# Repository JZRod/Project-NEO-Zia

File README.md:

# Project NEO Zia
This circut board is intended to make the New Mexico Zia out of LED's 
There is a [PDF](assets/README.pdf) version of this doccument in the assets folder

## Using the board
This section goes over information on how to configure, wire, and mount the board. 
### Configuration
This PCB is designed to accept power from an external 12 volt input. It is also able to recieve power from a 5 volt PWM cable. By default the board is configured to recieve power from the 12 volt external power input.  
- For the PWM power input open JP1 and bridge JP2
- For external power input open JP2 and bridge JP1  

> **NEVER BRIDGE BOTH JUMPERS AT ONCE**
### Wiring
#### External Power Input
The external power input can accept voltages between 5 and 12 volts. When using the external power input fuse it at a maximum of 5 amps.  

#### PWM Connections
There are two PWM connections on the board. One is a PWM output and one is an input. The output connector outputs a PWM signal after it has passed through all LED's. If you want to power the board with the PWM connection refer to the configuration section of this doccument.  

>- The PWM output connector outputs whatever voltage it is provided through the PWM input  
>- The PWM output **does not touch the voltage regulator on the board at all**  
>- The pinout of these connectors is also labeled on the board  
### Programming
This board uses a standard NeoPixel PWM signal. The PWM output connector is connected to the DATA OUT pin on the last NeoPixel in the chain. The PWM input connector is connected to the DATA IN pin on the first NeoPixel in the chain. 
> The DATA IN/OUT pins do not have any protection on them  
>   The pinout for the PWM In/Out connecters can be seen in the Wiring section of this document
More information about these NeoPixels can be found in their [datasheet](https://cdn-shop.adafruit.com/product-files/1655/SKC6812RV__12VOP0274E_REV.A1_EN%2812%29.pdf)
#### NeoPixel Layout
The drawing below shous the pattern in which the NeoPixels are wired  
The PWM Input is connected to D68 and goes to each NeoPixel in a decreasing order. When the signal reaches D1 it is connected to the PWM Output connector.  

The black line starts at D68 and goes around the board in the same way the PWM signal is routed until it reaches D1.
> The DATA Out pin of D1 is wired to Pin 3 of the PWM Output Connector
### Mounting
On the newest revisions the 4 center holes are 3/16 and sized for 10/24 screws. Each revision has a STEP file in it's folder.  
> For all revisions, I would suggest that you check the mounting hole spacing and size in the CAD model
## Manufacturing
If you want to make this board you can either use the pre-made gerber files or customize them using the KiCad project files. All these files are available in the revision folders. The latest version can also be found on the releases page.
### Pre-Made Gerbers
In each revision folder there are zip files. These are the Gerber's, and you should be able to drop them straight in you PCB manufacturing service.  
> Some PCB manufacturing services will accept the bare KiCad PCB file.   
>**Read the REVISION NOTES.txt for info on what changed between each revision** 
### Customization  
If you want to customize this board each revision folder has a KiCad project file, a KiCad PCB File, and a KiCad Schematic file. 
> I suggest you use KiCad 9 or higher.  
>**Read the [REVISION NOTES.txt](Revisions/REVISION$20NOTES.txt) for info on what changed between each revision**  
## Credit  
**Designed by Josh Rodriguez for FIRST Robotics Competition Team 1164 Project NEO**

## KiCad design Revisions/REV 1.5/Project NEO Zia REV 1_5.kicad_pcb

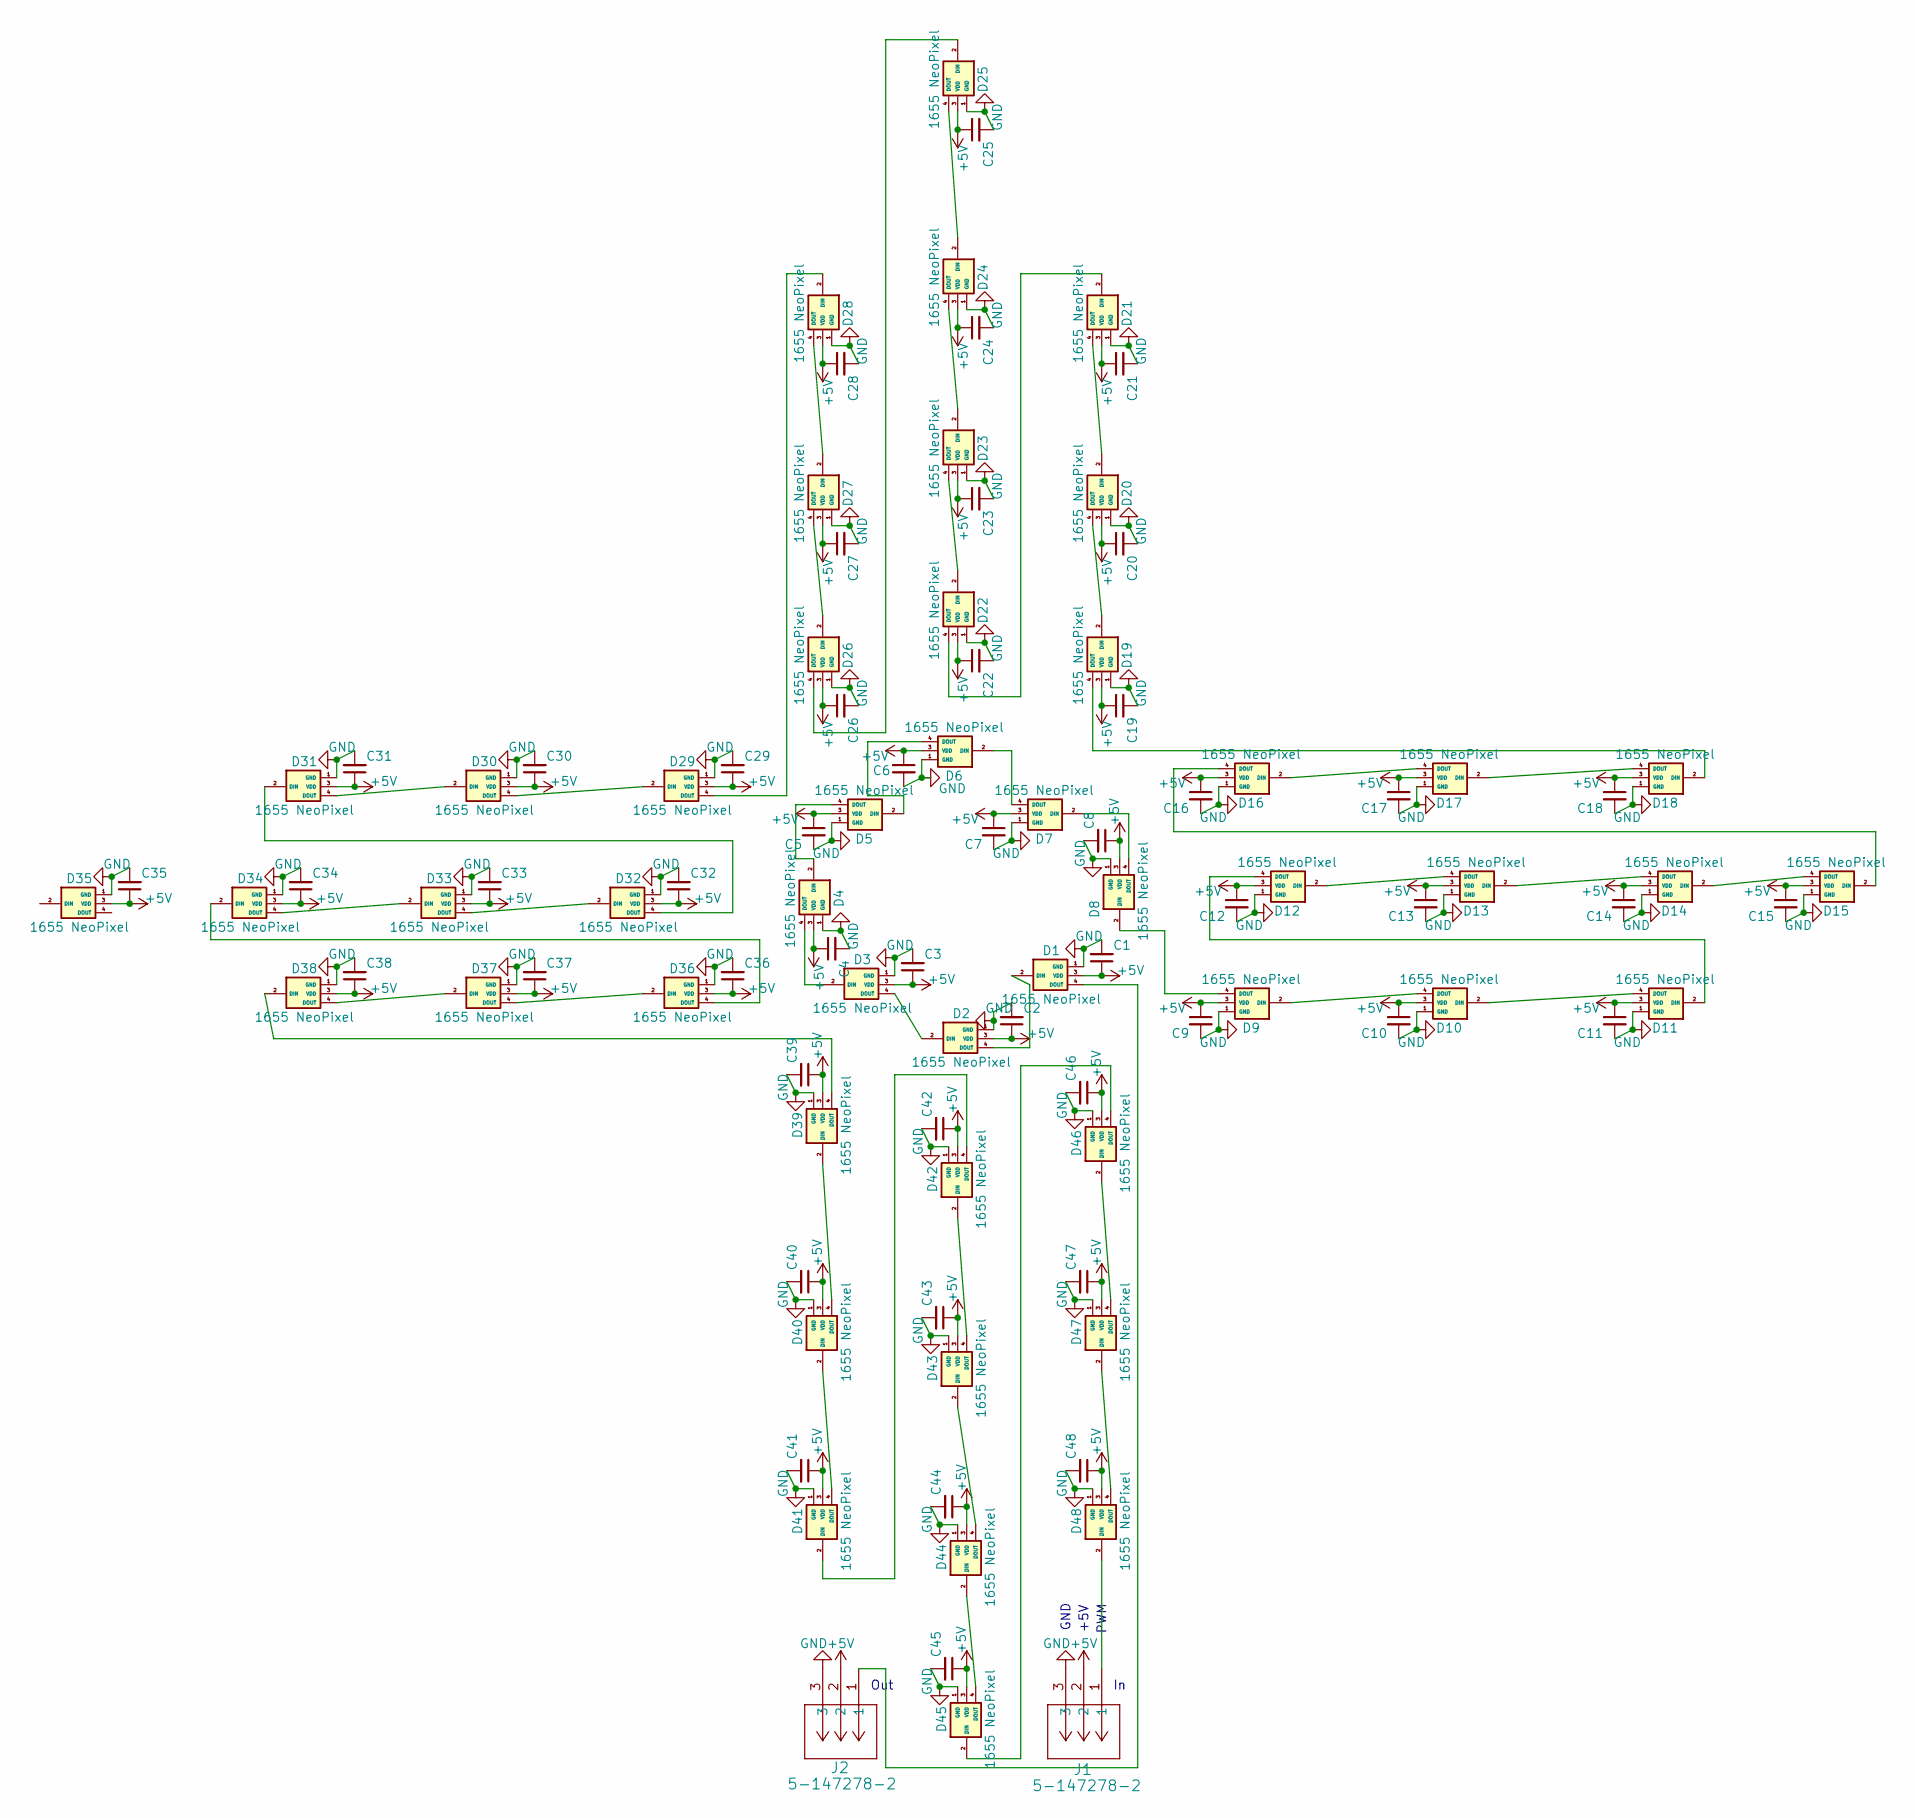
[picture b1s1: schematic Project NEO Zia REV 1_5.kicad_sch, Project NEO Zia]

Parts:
C1, C2, C3, C4, C5, C6, C7, C8, C9, C10, C11, C12, C13, C14, C15, C16, C17, C18, C19, C20, C21, C22, C23, C24, C25, C26, C27, C28, C29, C30, C31, C32, C33, C34, C35, C36, C37, C38, C39, C40, C41, C42, C43, C44, C45, C46, C47, C48: C_Small; CAPC1005X55N
D1, D2, D3, D4, D5, D6, D7, D8, D9, D10, D11, D12, D13, D14, D15, D16, D17, D18, D19, D20, D21, D22, D23, D24, D25, D26, D27, D28, D29, D30, D31, D32, D33, D34, D35, D36, D37, D38, D39, D40, D41, D42, D43, D44, D45, D46, D47, D48: 1655 NeoPixel; LED_1655; PARTREV 01
J1, J2: 5-147278-2; CONN3_5-147278-2_TEC

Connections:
+5V: C1.1, C2.1, C3.1, C4.1, C5.1, C6.1, C7.1, C8.1, C9.1, C10.1, C11.1, C12.1, C13.1, C14.1, C15.1, C16.1, C17.1, C18.1, C19.1, C20.1, C21.1, C22.1, C23.1, C24.1, C25.1, C26.1, C27.1, C28.1, C29.1, C30.1, C31.1, C32.1, C33.1, C34.1, C35.1, C36.1, C37.1, C38.1, C39.1, C40.1, C41.1, C42.1, C43.1, C44.1, C45.1, C46.1, C47.1, C48.1, D1.3 (VDD), D2.3 (VDD), D3.3 (VDD), D4.3 (VDD), D5.3 (VDD), D6.3 (VDD), D7.3 (VDD), D8.3 (VDD), D9.3 (VDD), D10.3 (VDD), D11.3 (VDD), D12.3 (VDD), D13.3 (VDD), D14.3 (VDD), D15.3 (VDD), D16.3 (VDD), D17.3 (VDD), D18.3 (VDD), D19.3 (VDD), D20.3 (VDD), D21.3 (VDD), D22.3 (VDD), D23.3 (VDD), D24.3 (VDD), D25.3 (VDD), D26.3 (VDD), D27.3 (VDD), D28.3 (VDD), D29.3 (VDD), D30.3 (VDD), D31.3 (VDD), D32.3 (VDD), D33.3 (VDD), D34.3 (VDD), D35.3 (VDD), D36.3 (VDD), D37.3 (VDD), D38.3 (VDD), D39.3 (VDD), D40.3 (VDD), D41.3 (VDD), D42.3 (VDD), D43.3 (VDD), D44.3 (VDD), D45.3 (VDD), D46.3 (VDD), D47.3 (VDD), D48.3 (VDD), J1.2, J2.2
GND: C1.2, C2.2, C3.2, C4.2, C5.2, C6.2, C7.2, C8.2, C9.2, C10.2, C11.2, C12.2, C13.2, C14.2, C15.2, C16.2, C17.2, C18.2, C19.2, C20.2, C21.2, C22.2, C23.2, C24.2, C25.2, C26.2, C27.2, C28.2, C29.2, C30.2, C31.2, C32.2, C33.2, C34.2, C35.2, C36.2, C37.2, C38.2, C39.2, C40.2, C41.2, C42.2, C43.2, C44.2, C45.2, C46.2, C47.2, C48.2, D1.1 (GND), D2.1 (GND), D3.1 (GND), D4.1 (GND), D5.1 (GND), D6.1 (GND), D7.1 (GND), D8.1 (GND), D9.1 (GND), D10.1 (GND), D11.1 (GND), D12.1 (GND), D13.1 (GND), D14.1 (GND), D15.1 (GND), D16.1 (GND), D17.1 (GND), D18.1 (GND), D19.1 (GND), D20.1 (GND), D21.1 (GND), D22.1 (GND), D23.1 (GND), D24.1 (GND), D25.1 (GND), D26.1 (GND), D27.1 (GND), D28.1 (GND), D29.1 (GND), D30.1 (GND), D31.1 (GND), D32.1 (GND), D33.1 (GND), D34.1 (GND), D35.1 (GND), D36.1 (GND), D37.1 (GND), D38.1 (GND), D39.1 (GND), D40.1 (GND), D41.1 (GND), D42.1 (GND), D43.1 (GND), D44.1 (GND), D45.1 (GND), D46.1 (GND), D47.1 (GND), D48.1 (GND), J1.3, J2.3
unnamed: D1.2 (DIN), D2.4 (DOUT)
unnamed: D1.4 (DOUT), J2.1
unnamed: D2.2 (DIN), D3.4 (DOUT)
unnamed: D3.2 (DIN), D4.4 (DOUT)
unnamed: D4.2 (DIN), D5.4 (DOUT)
unnamed: D5.2 (DIN), D6.4 (DOUT)
unnamed: D6.2 (DIN), D7.4 (DOUT)
unnamed: D7.2 (DIN), D8.4 (DOUT)
unnamed: D8.2 (DIN), D9.4 (DOUT)
unnamed: D10.2 (DIN), D11.4 (DOUT)
unnamed: D9.2 (DIN), D10.4 (DOUT)
unnamed: D11.2 (DIN), D12.4 (DOUT)
unnamed: D12.2 (DIN), D13.4 (DOUT)
unnamed: D13.2 (DIN), D14.4 (DOUT)
unnamed: D14.2 (DIN), D15.4 (DOUT)
unnamed: D15.2 (DIN), D16.4 (DOUT)
unnamed: D16.2 (DIN), D17.4 (DOUT)
unnamed: D17.2 (DIN), D18.4 (DOUT)
unnamed: D18.2 (DIN), D19.4 (DOUT)
unnamed: D19.2 (DIN), D20.4 (DOUT)
unnamed: D20.2 (DIN), D21.4 (DOUT)
unnamed: D21.2 (DIN), D22.4 (DOUT)
unnamed: D22.2 (DIN), D23.4 (DOUT)
unnamed: D23.2 (DIN), D24.4 (DOUT)
unnamed: D24.2 (DIN), D25.4 (DOUT)
unnamed: D25.2 (DIN), D26.4 (DOUT)
unnamed: D26.2 (DIN), D27.4 (DOUT)
unnamed: D27.2 (DIN), D28.4 (DOUT)
unnamed: D28.2 (DIN), D29.4 (DOUT)
unnamed: D29.2 (DIN), D30.4 (DOUT)
unnamed: D30.2 (DIN), D31.4 (DOUT)
unnamed: D31.2 (DIN), D32.4 (DOUT)
unnamed: D32.2 (DIN), D33.4 (DOUT)
unnamed: D33.2 (DIN), D34.4 (DOUT)
unnamed: D34.2 (DIN), D36.4 (DOUT)
unnamed: D36.2 (DIN), D37.4 (DOUT)
unnamed: D37.2 (DIN), D38.4 (DOUT)
unnamed: D38.2 (DIN), D39.4 (DOUT)
unnamed: D39.2 (DIN), D40.4 (DOUT)
unnamed: D40.2 (DIN), D41.4 (DOUT)
unnamed: D41.2 (DIN), D42.4 (DOUT)
unnamed: D42.2 (DIN), D43.4 (DOUT)
unnamed: D43.2 (DIN), D44.4 (DOUT)
unnamed: D44.2 (DIN), D45.4 (DOUT)
unnamed: D45.2 (DIN), D46.4 (DOUT)
unnamed: D46.2 (DIN), D47.4 (DOUT)
unnamed: D47.2 (DIN), D48.4 (DOUT)
unnamed: D48.2 (DIN), J1.1

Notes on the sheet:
PWM
GND
Out
+5V

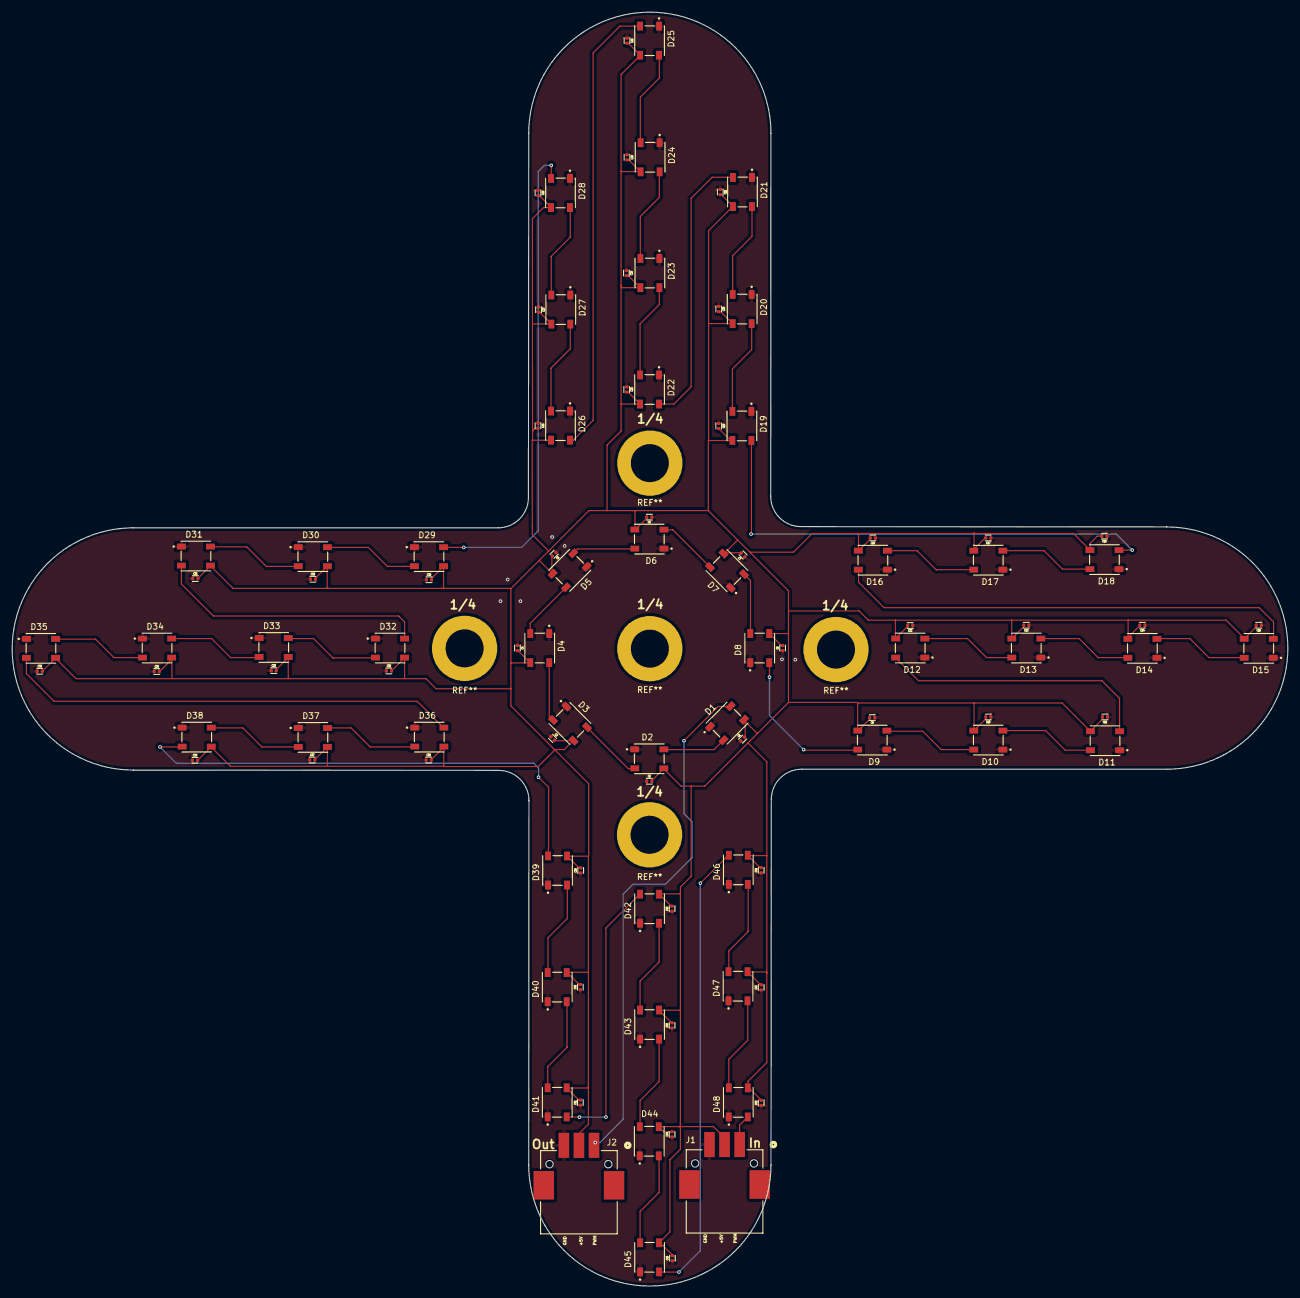
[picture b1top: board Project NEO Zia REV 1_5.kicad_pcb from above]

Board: 2 copper layers, 214.8 x 214.5 mm, 98 parts (0 on the bottom side), 50 nets.

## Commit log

2025-10-10 Added all custom parts and project files
2025-10-10 Update README.md
    Fixed formatting issue
2025-10-10 Update README.md
    Fixed spelling mistakes
    Specified FRC instead of just FIRST Robotics
2025-10-10 Updated REV 1 to have STEP file and Gerber zip
2025-10-10 Removed unessacary files
2025-10-10 Added Gerber and STEP files Removed un-needed files Updated sheet information
2025-10-10 - Added "For more info visit: https://github.com/JZRod/Project-NEO-Zia" to all versions # backported to all pre-existing versions - Fixed voltage regulator tab being shorted to GND # Backported to al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
2025-10-10 Moved all Work In Progress Files to Work In Progress folder
2025-10-10 Updated README.md and added new backup file
2025-10-10 Update README.md
    Fixed some spelling mistakes
2025-10-10 Updated README.md and added a PDF and DOCX version
2025-10-10 Delete assets/configtable.png
    Removed unnecessary file
2025-10-14 Update README.md
    Added info about programming
2025-10-14 Add files via upload
    Added image that shows how the board's PWM is routed
2025-10-14 Update README.md
    Fixed issue with the image file for programming section not displaying
2025-10-14 Add files via upload
    Updated JumperConfigTable.png and PWM Pinout.png
2025-10-14 Updated PWM Pinout.png
2025-10-14 Updated PWM Pinout.png for the 3rd time
2025-10-14 Updated PWM Pinout.png
    Hopefully for the last time today
2025-10-14 Updated PWM Pinout.png
    i think it will work this time
2025-10-14 Updated PWM Pinout.png
    I was wrong it was not the last time I would updated this
2026-02-17 - Added 5V copper plane in center for TI LM1084 voltage regulator - Rearranged filter capacitors for voltage regulator and some NeoPixel's - Added REV marker to board # On Rear Silkscreen - Added Jum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
2026-02-17 Added hyperlink to revision notes txt file
2026-02-17 Fix link formatting in README.md
2026-02-17 Fix link formatting in README.md again
2026-02-17 Fixed formatting issues
